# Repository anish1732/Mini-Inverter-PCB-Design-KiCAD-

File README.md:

# Mini Inverter PCB Design

This repository contains the complete KiCad project files, schematics, PCB layout, and fabrication outputs for a **mini inverter circuit**.  
The design converts DC input into AC output using MOSFET switching and driver ICs, optimized for compact size and efficient performance.

---

## 📂 Repository Contents
- **/design** → KiCad schematic (`.sch`) and PCB layout (`.kicad_pcb`)
- **/fabrication** → Gerber files for PCB manufacturing
- **/bom** → Bill of Materials (BOM) for component sourcing

---

## ⚡ Features
- Two-layer PCB with copper fills for improved grounding and thermal management
- MOSFET-based inverter topology with driver ICs
- DRC/ERC checks performed for manufacturability
- Ready-to-fabricate Gerber outputs
- Open-source hardware license for community use and modification

---

## 🛠️ How to Use
1. Clone or download this repository.
2. Open the KiCad project in **KiCad v7 or later**.
3. Run **ERC/DRC checks** to verify design integrity.
4. Use the provided Gerber files for PCB fabrication.
5. Refer to the BOM for component sourcing.

---

## 📜 License
This project is released under the **MIT License**.  
You are free to use, modify, and distribute the design, provided proper attribution is given.

---

## 👤 Author
Designed by **Anish Kumar(https://github.com/anish1732)**

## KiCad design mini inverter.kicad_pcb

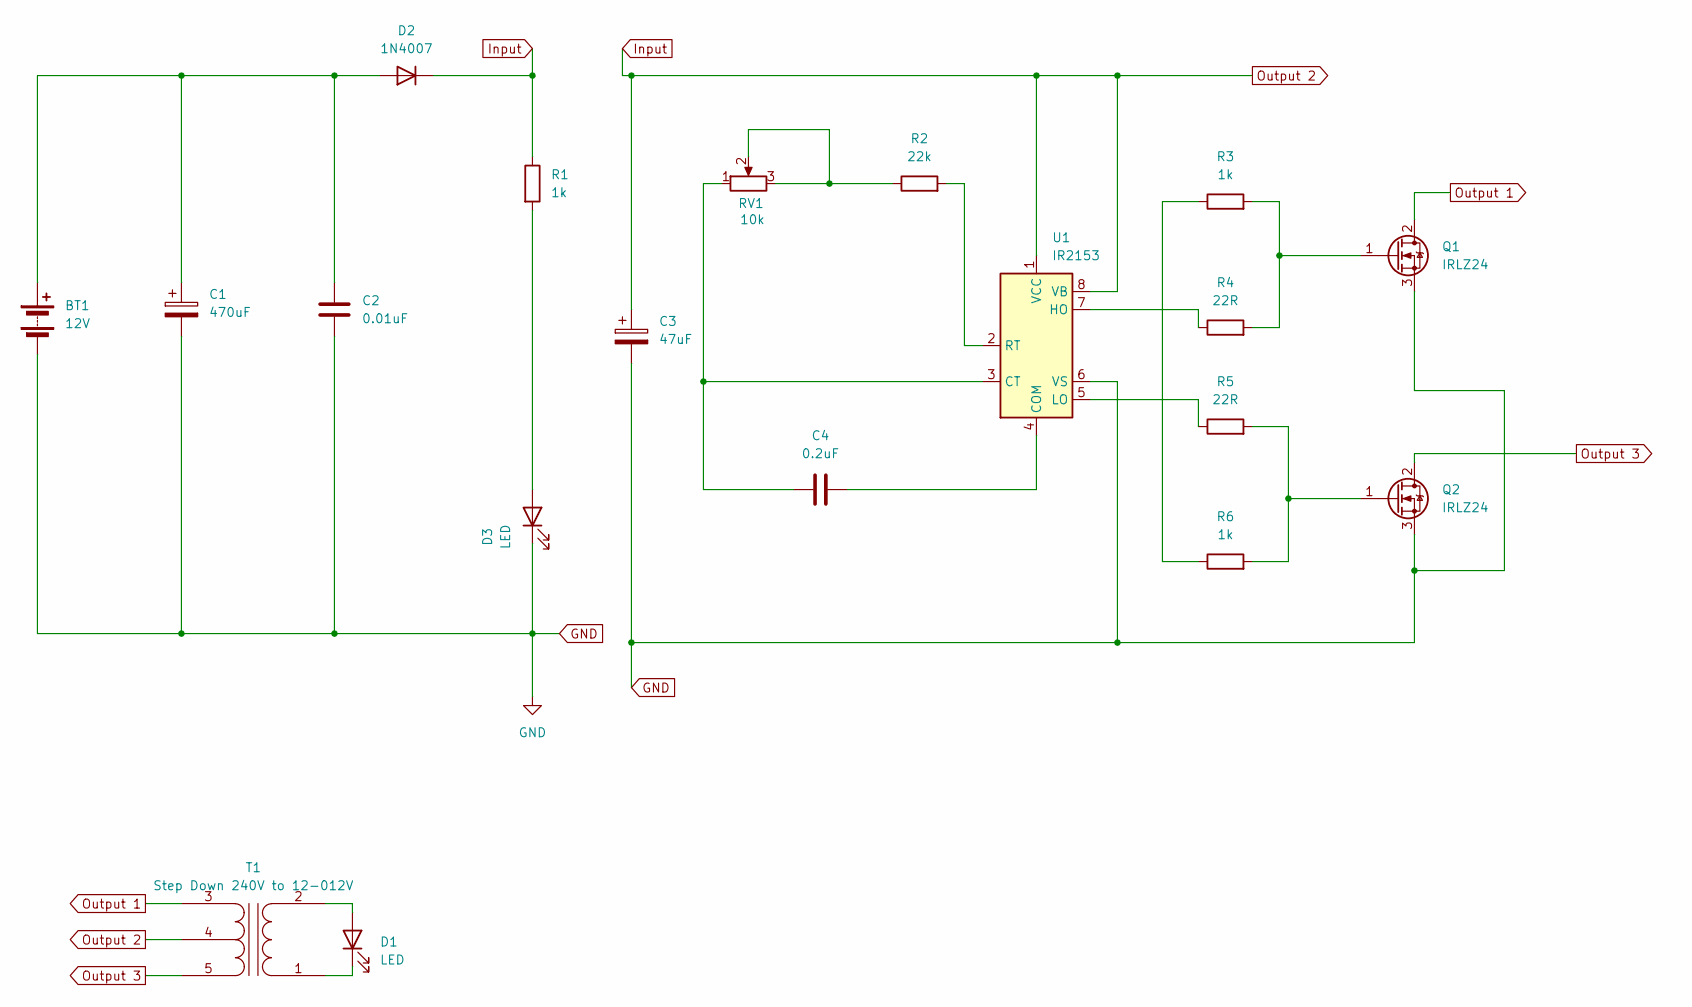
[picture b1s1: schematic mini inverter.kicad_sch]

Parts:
BT1: 12V; TerminalBlock_Xinya_XY308-2.54-2P_1x02_P2.54mm_Horizontal
C1: 470uF; CP_Radial_D6.3mm_P2.50mm
C2: 0.01uF; C_Disc_D3.0mm_W1.6mm_P2.50mm
C3: 47uF; CP_Radial_D5.0mm_P2.50mm
C4: 0.2uF; C_Disc_D3.0mm_W1.6mm_P2.50mm
D1, D3: LED; LED_D5.0mm
D2: 1N4007; D_DO-41_SOD81_P10.16mm_Horizontal
Q1, Q2: IRLZ24; TO-220-3_Vertical
R1, R3, R6: 1k; R_Axial_DIN0204_L3.6mm_D1.6mm_P5.08mm_Horizontal
R2: 22k; R_Axial_DIN0204_L3.6mm_D1.6mm_P5.08mm_Horizontal
R4, R5: 22R; R_Axial_DIN0204_L3.6mm_D1.6mm_P5.08mm_Horizontal
RV1: 10k; Potentiometer_ACP_CA6-H2,5_Horizontal
T1: Step Down 240V to 12-012V; TerminalBlock_Xinya_XY308-2.54-5P_1x05_P2.54mm_Horizontal
U1: IR2153; DIP-8_W7.62mm

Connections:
GND: BT1.2 (-), C1.2, C2.2, C3.2, D3.1 (K), Q1.3 (S), Q2.3 (S), U1.6 (VS)
Input: C3.1, D2.1 (K), R1.1, T1.4 (SC), U1.1 (VCC), U1.8 (VB)
unnamed: BT1.1 (+), C1.1, C2.1, D2.2 (A)
unnamed: D1.2 (A), T1.2 (AB)
unnamed: D1.1 (K), T1.1 (AA)
unnamed: D3.2 (A), R1.2
unnamed: Q1.1 (G), R3.2, R4.2
unnamed: Q2.1 (G), R5.2, R6.2
unnamed: R2.1, RV1.2, RV1.3
unnamed: R3.1, R6.1
unnamed: C4.1, U1.4 (COM)
unnamed: C4.2, RV1.1, U1.3 (CT)
unnamed: R4.1, U1.7 (HO)
unnamed: R5.1, U1.5 (LO)
unnamed: R2.2, U1.2 (RT)
Output 1: Q1.2 (D), T1.3 (SA)
Output 3: Q2.2 (D), T1.5 (SB)

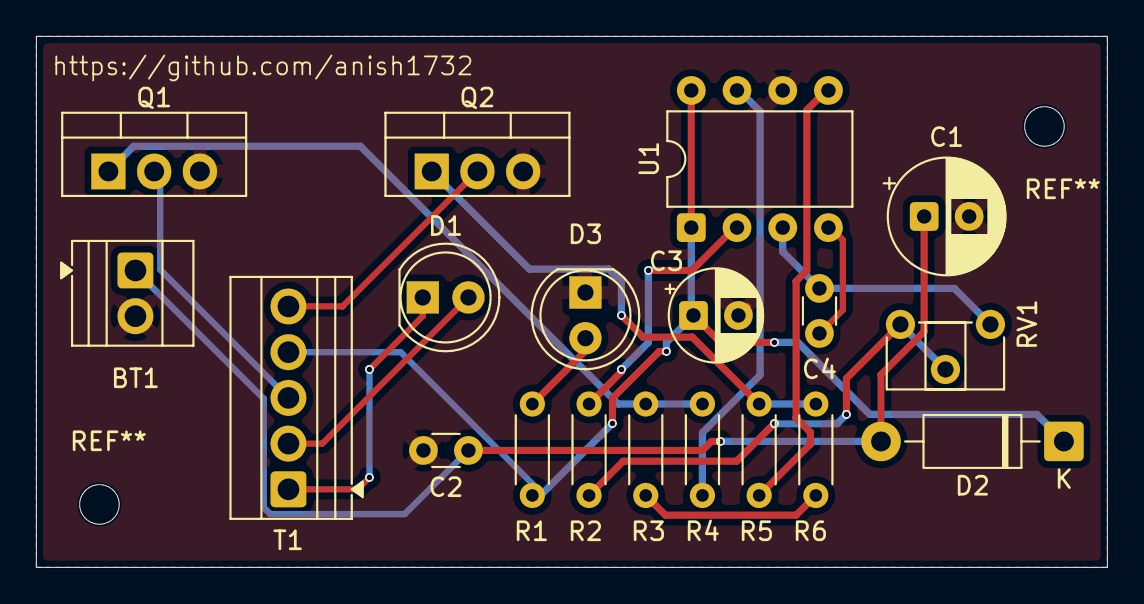
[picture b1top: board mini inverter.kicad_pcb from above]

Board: 2 copper layers, 59.5 x 29.5 mm, 19 parts (0 on the bottom side), 17 nets.

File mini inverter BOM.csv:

"Reference","Qty","Value","DNP","Exclude from BOM","Exclude from Board","Footprint","Datasheet"
"BT1","1","12V","","","","TerminalBlock:TerminalBlock_Xinya_XY308-2.54-2P_1x02_P2.54mm_Horizontal",""
"C1","1","470uF","","","","Capacitor_THT:CP_Radial_D6.3mm_P2.50mm",""
"C2","1","0.01uF","","","","Capacitor_THT:C_Disc_D3.0mm_W1.6mm_P2.50mm",""
"C3","1","47uF","","","","Capacitor_THT:CP_Radial_D5.0mm_P2.50mm",""
"C4","1","0.2uF","","","","Capacitor_THT:C_Disc_D3.0mm_W1.6mm_P2.50mm",""
"D1,D3","2","LED","","","","LED_THT:LED_D5.0mm",""
"D2","1","1N4007","","","","Diode_THT:D_DO-41_SOD81_P10.16mm_Horizontal","http://www.vishay.com/docs/88503/1n4001.pdf"
"Q1,Q2","2","IRLZ24","","","","Package_TO_SOT_THT:TO-220-3_Vertical","https://www.vishay.com/docs/91326/sihlz24.pdf"
"R1,R3,R6","3","1k","","","","Resistor_THT:R_Axial_DIN0204_L3.6mm_D1.6mm_P5.08mm_Horizontal",""
"R2","1","22k","","","","Resistor_THT:R_Axial_DIN0204_L3.6mm_D1.6mm_P5.08mm_Horizontal",""
"R4,R5","2","22R","","","","Resistor_THT:R_Axial_DIN0204_L3.6mm_D1.6mm_P5.08mm_Horizontal",""
"RV1","1","10k","","","","Potentiometer_THT:Potentiometer_ACP_CA6-H2,5_Horizontal",""
"T1","1","Step Down 240V to 12-012V","","","","TerminalBlock:TerminalBlock_Xinya_XY308-2.54-5P_1x05_P2.54mm_Horizontal",""
"U1","1","IR2153","","","","Package_DIP:DIP-8_W7.62mm","https://www.infineon.com/dgdl/ir2153.pdf?fileId=5546d4625336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"

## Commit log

2026-06-23 Add files via upload
    Bill of materials for sourcing the components easily.
2026-06-23 Revise README with new structure and content
    Updated README to improve formatting and add sections.
